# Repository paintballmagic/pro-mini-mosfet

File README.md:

# pro-mini-mosfet
A electronic paintball gun sheild for the Arduino Pro Mini/ pneumatic solenoid driver

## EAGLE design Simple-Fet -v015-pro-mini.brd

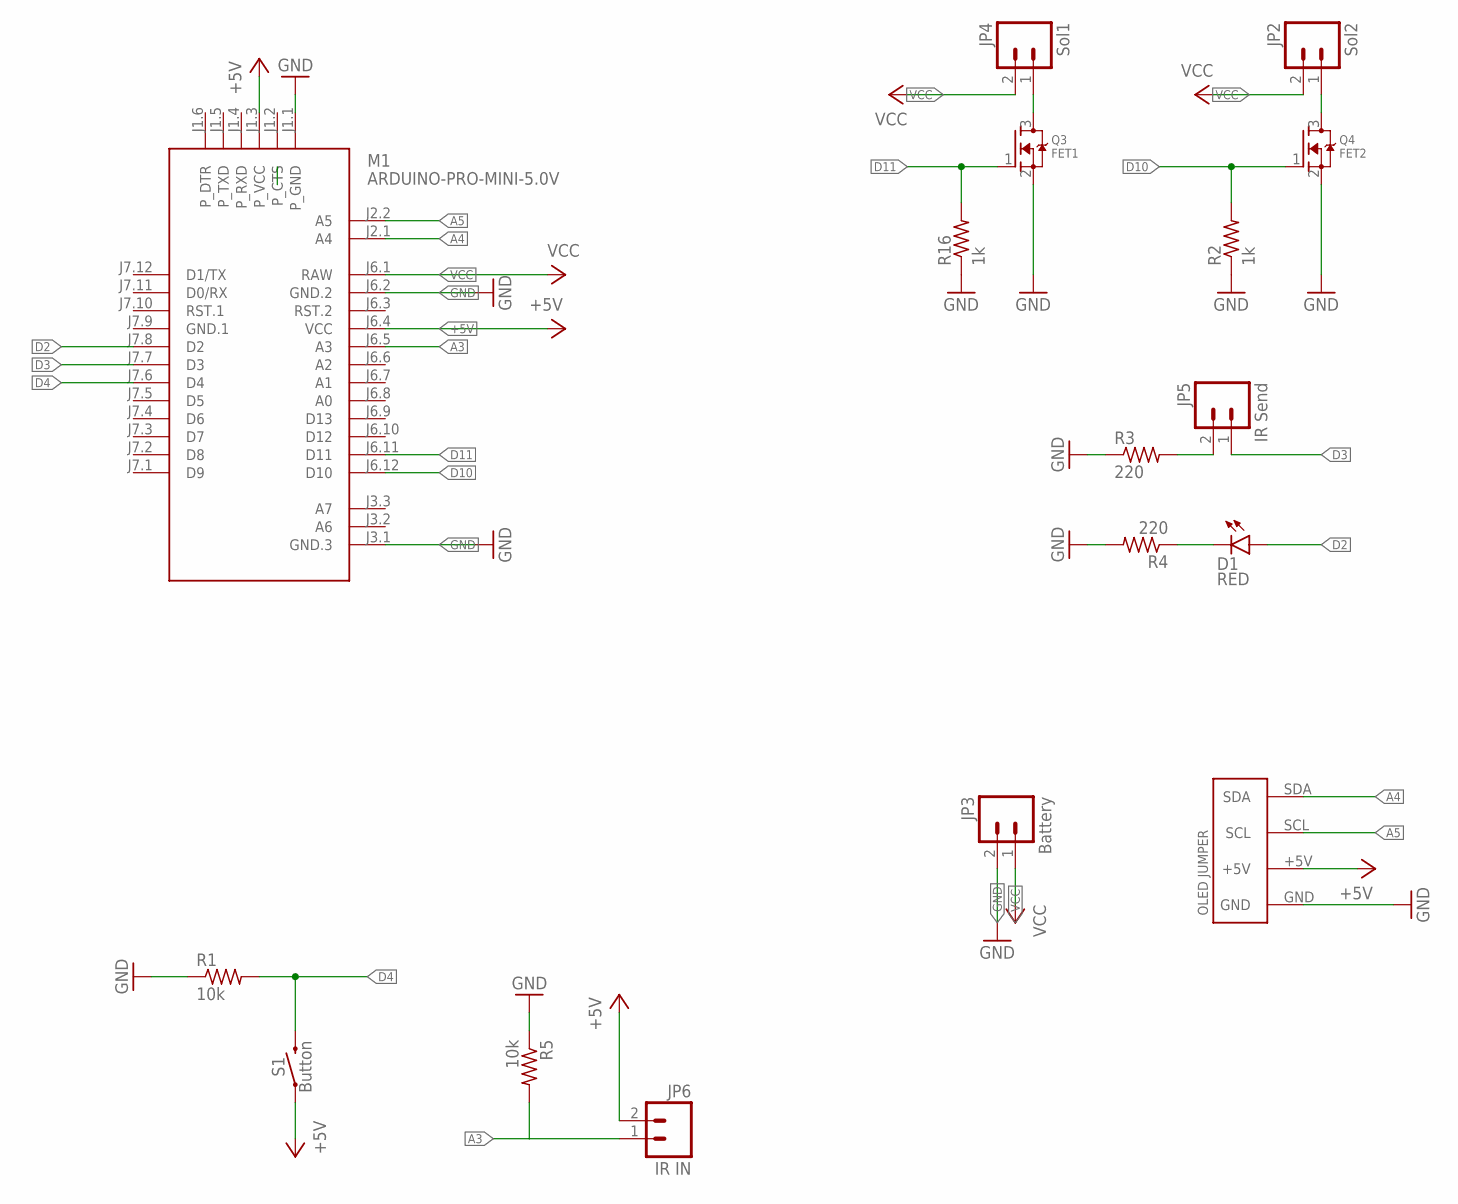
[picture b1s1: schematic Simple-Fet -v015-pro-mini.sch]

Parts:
D1: RED; LED-1206; MPN HSMC-C150
JP2: Sol2; 1X02; MPN 22-23-2021
JP3: Battery; 1X02; MPN 2239
JP4: Sol1; 1X02; MPN 22-23-2021
JP5: IR Send; 1X02; MPN QEE122
JP6: IR IN; 1X02; MPN QEE113
M1: ARDUINO-PRO-MINI-5.0V; ARDUINO-PRO-MINI
Q3: FET1; SOT23; MPN SI2392ADS-T1-GE3
Q4: FET2; SOT23; MPN SI2392ADS-T1-GE3
R1, R5: 10k; M1206; MPN MC1206S4F1002T5E
R2, R16: 1k; M1206; MPN RT1206FRE071KL
R3, R4: 220; M1206; MPN CR1206FX2200ELF
S1: Button; TACTILE_SWITCH_SMD_6.0X3.5MM
U$2: OLEDHEADER; OLED-CON

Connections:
+5V: JP6.2, M1.J1.3 (P_VCC), M1.J6.4 (VCC), S1.1, U$2.+5V
A3: JP6.1, M1.J6.5 (A3), R5.2
A4: M1.J2.1 (A4), U$2.SDA
A5: M1.J2.2 (A5), U$2.SCL
D2: D1.A, M1.J7.8 (D2)
D3: JP5.1, M1.J7.7 (D3)
D4: M1.J7.6 (D4), R1.2, S1.2
D10: M1.J6.12 (D10), Q4.1 (G), R2.2
D11: M1.J6.11 (D11), Q3.1 (G), R16.2
GND: JP3.2, M1.J1.1 (P_GND), M1.J3.1 (GND.3), M1.J6.2 (GND.2), Q3.2 (S), Q4.2 (S), R1.1, R2.1, R3.1, R4.2, R5.1, R16.1, U$2.GND
GND.1: M1.J7.9 (GND.1)
M1: JP4.1, Q3.3 (D)
M2: JP2.1, Q4.3 (D)
unnamed: D1.C, R4.1
unnamed: JP5.2, R3.2
VCC: JP2.2, JP3.1, JP4.2, M1.J6.1 (RAW)

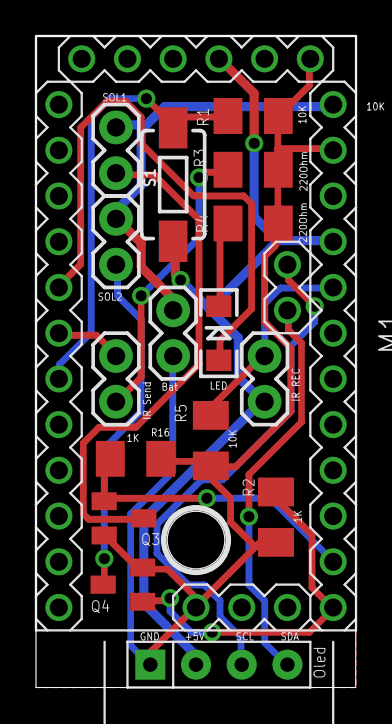
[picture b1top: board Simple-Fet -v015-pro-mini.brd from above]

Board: 2 copper layers, 17.8 x 36.2 mm, 17 parts (0 on the bottom side), 15 nets.

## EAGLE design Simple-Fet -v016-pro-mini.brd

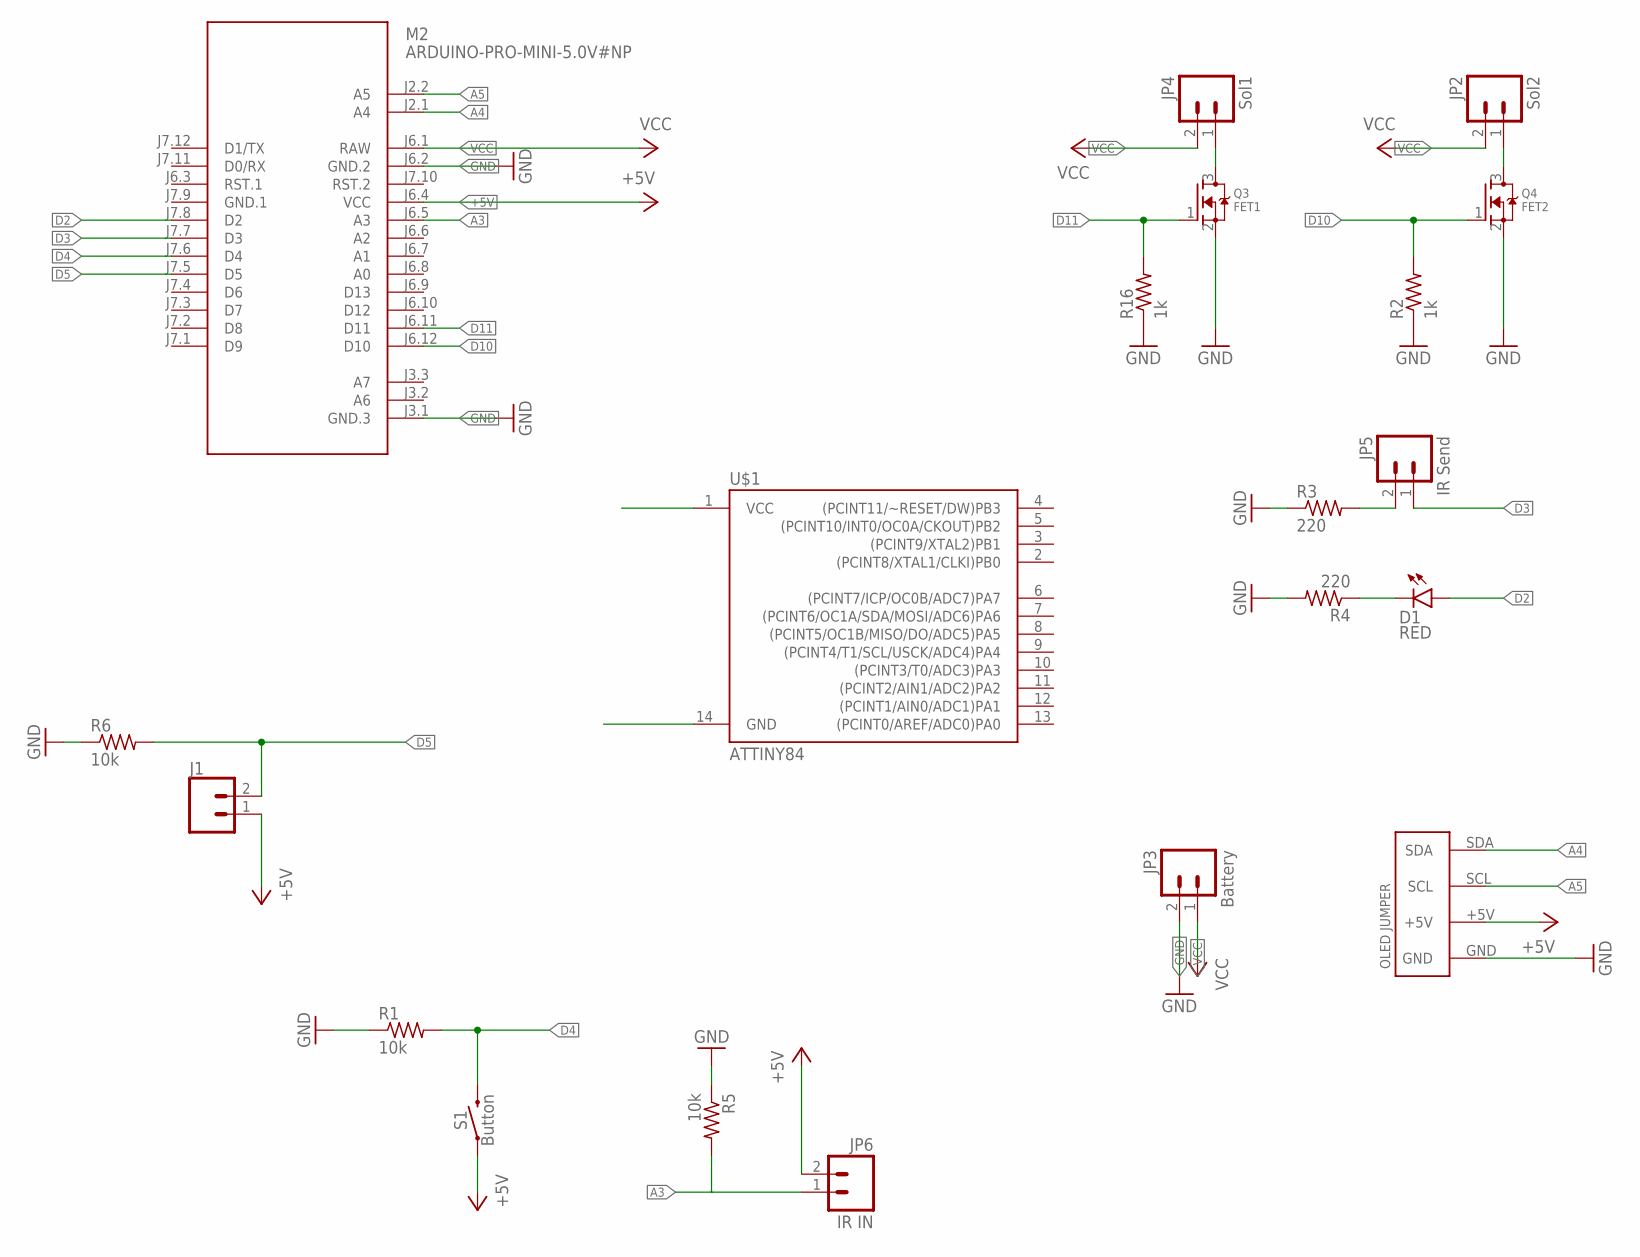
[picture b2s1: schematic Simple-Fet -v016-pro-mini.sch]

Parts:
D1: RED; LED-1206; MPN HSMC-C150
J1: CONN_02POGO_PIN_HOLES_ONLY; 1X02_PP_HOLES_ONLY
JP2: Sol2; 1X02; MPN 22-23-2021
JP3: Battery; 1X02; MPN 2239
JP4: Sol1; 1X02; MPN 22-23-2021
JP5: IR Send; 1X02; MPN QEE122
JP6: IR IN; 1X02; MPN QEE113
M2: ARDUINO-PRO-MINI-5.0V#NP; ARDUINO-PRO-MINI#NP
Q3: FET1; SOT23; MPN SI2392ADS-T1-GE3
Q4: FET2; SOT23; MPN SI2392ADS-T1-GE3
R1, R5, R6: 10k; M1206; MPN MC1206S4F1002T5E
R2, R16: 1k; M1206; MPN RT1206FRE071KL
R3, R4: 220; M1206; MPN CR1206FX2200ELF
S1: Button; TACTILE_SWITCH_SMD_6.0X3.5MM
U$1: ATTINY84; SO14
U$2: OLEDHEADER; OLED-CON

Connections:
+5V: J1.1, JP6.2, M2.J6.4 (VCC), S1.1, U$2.+5V
A3: JP6.1, M2.J6.5 (A3), R5.2
A4: M2.J2.1 (A4), U$2.SDA
A5: M2.J2.2 (A5), U$2.SCL
D2: D1.A, M2.J7.8 (D2)
D3: JP5.1, M2.J7.7 (D3)
D4: M2.J7.6 (D4), R1.2, S1.2
D5: J1.2, M2.J7.5 (D5), R6.2
D10: M2.J6.12 (D10), Q4.1 (G), R2.2
D11: M2.J6.11 (D11), Q3.1 (G), R16.2
GND: JP3.2, M2.J3.1 (GND.3), M2.J6.2 (GND.2), Q3.2 (S), Q4.2 (S), R1.1, R2.1, R3.1, R4.2, R5.1, R6.1, R16.1, U$2.GND
GND.1: M2.J7.9 (GND.1)
M1: JP4.1, Q3.3 (D)
M2: JP2.1, Q4.3 (D)
unnamed: D1.C, R4.1
unnamed: JP5.2, R3.2
VCC: JP2.2, JP3.1, JP4.2, M2.J6.1 (RAW)

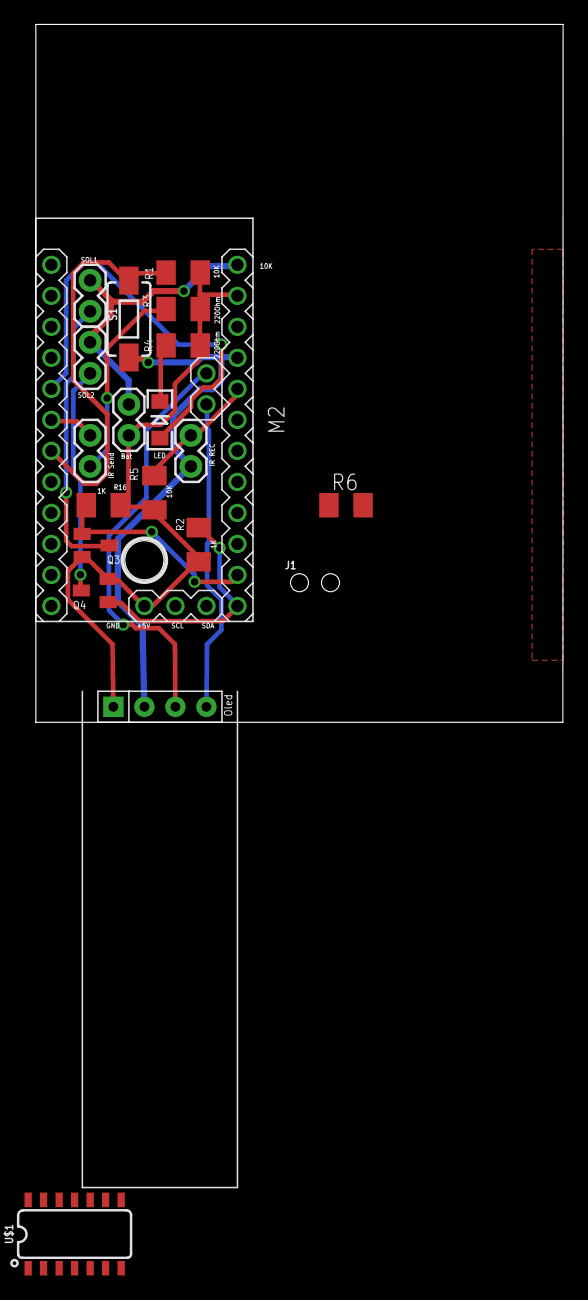
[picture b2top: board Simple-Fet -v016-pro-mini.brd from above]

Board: 2 copper layers, 43.2 x 57.1 mm, 20 parts (0 on the bottom side), 16 nets.

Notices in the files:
parts and their libraries:
SparkFun-Switches: Licensing: Creative Commons ShareAlike 4.0 International - https://creativecommons.org/licenses/by-sa/4.0
diy-modules: Released under the Creative Commons Attribution 4.0 International License: http://creativecommons.org/licenses/by/4.0
